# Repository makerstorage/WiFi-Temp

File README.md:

**WiFi Temperature Controller**

For more details, check out the product page at

http://makerstorage.com/index.php?id_product=27&controller=product

MakerStorage invests time and resources providing this open source design, please support MakerStorage and open-source hardware by purchasing products from MakerStorage!

Designed by MakerStorage LLC.

Creative Commons Attribution, Share-Alike license, check https://creativecommons.org/licenses/by-sa/3.0/ for more information All text above must be included in any redistribution

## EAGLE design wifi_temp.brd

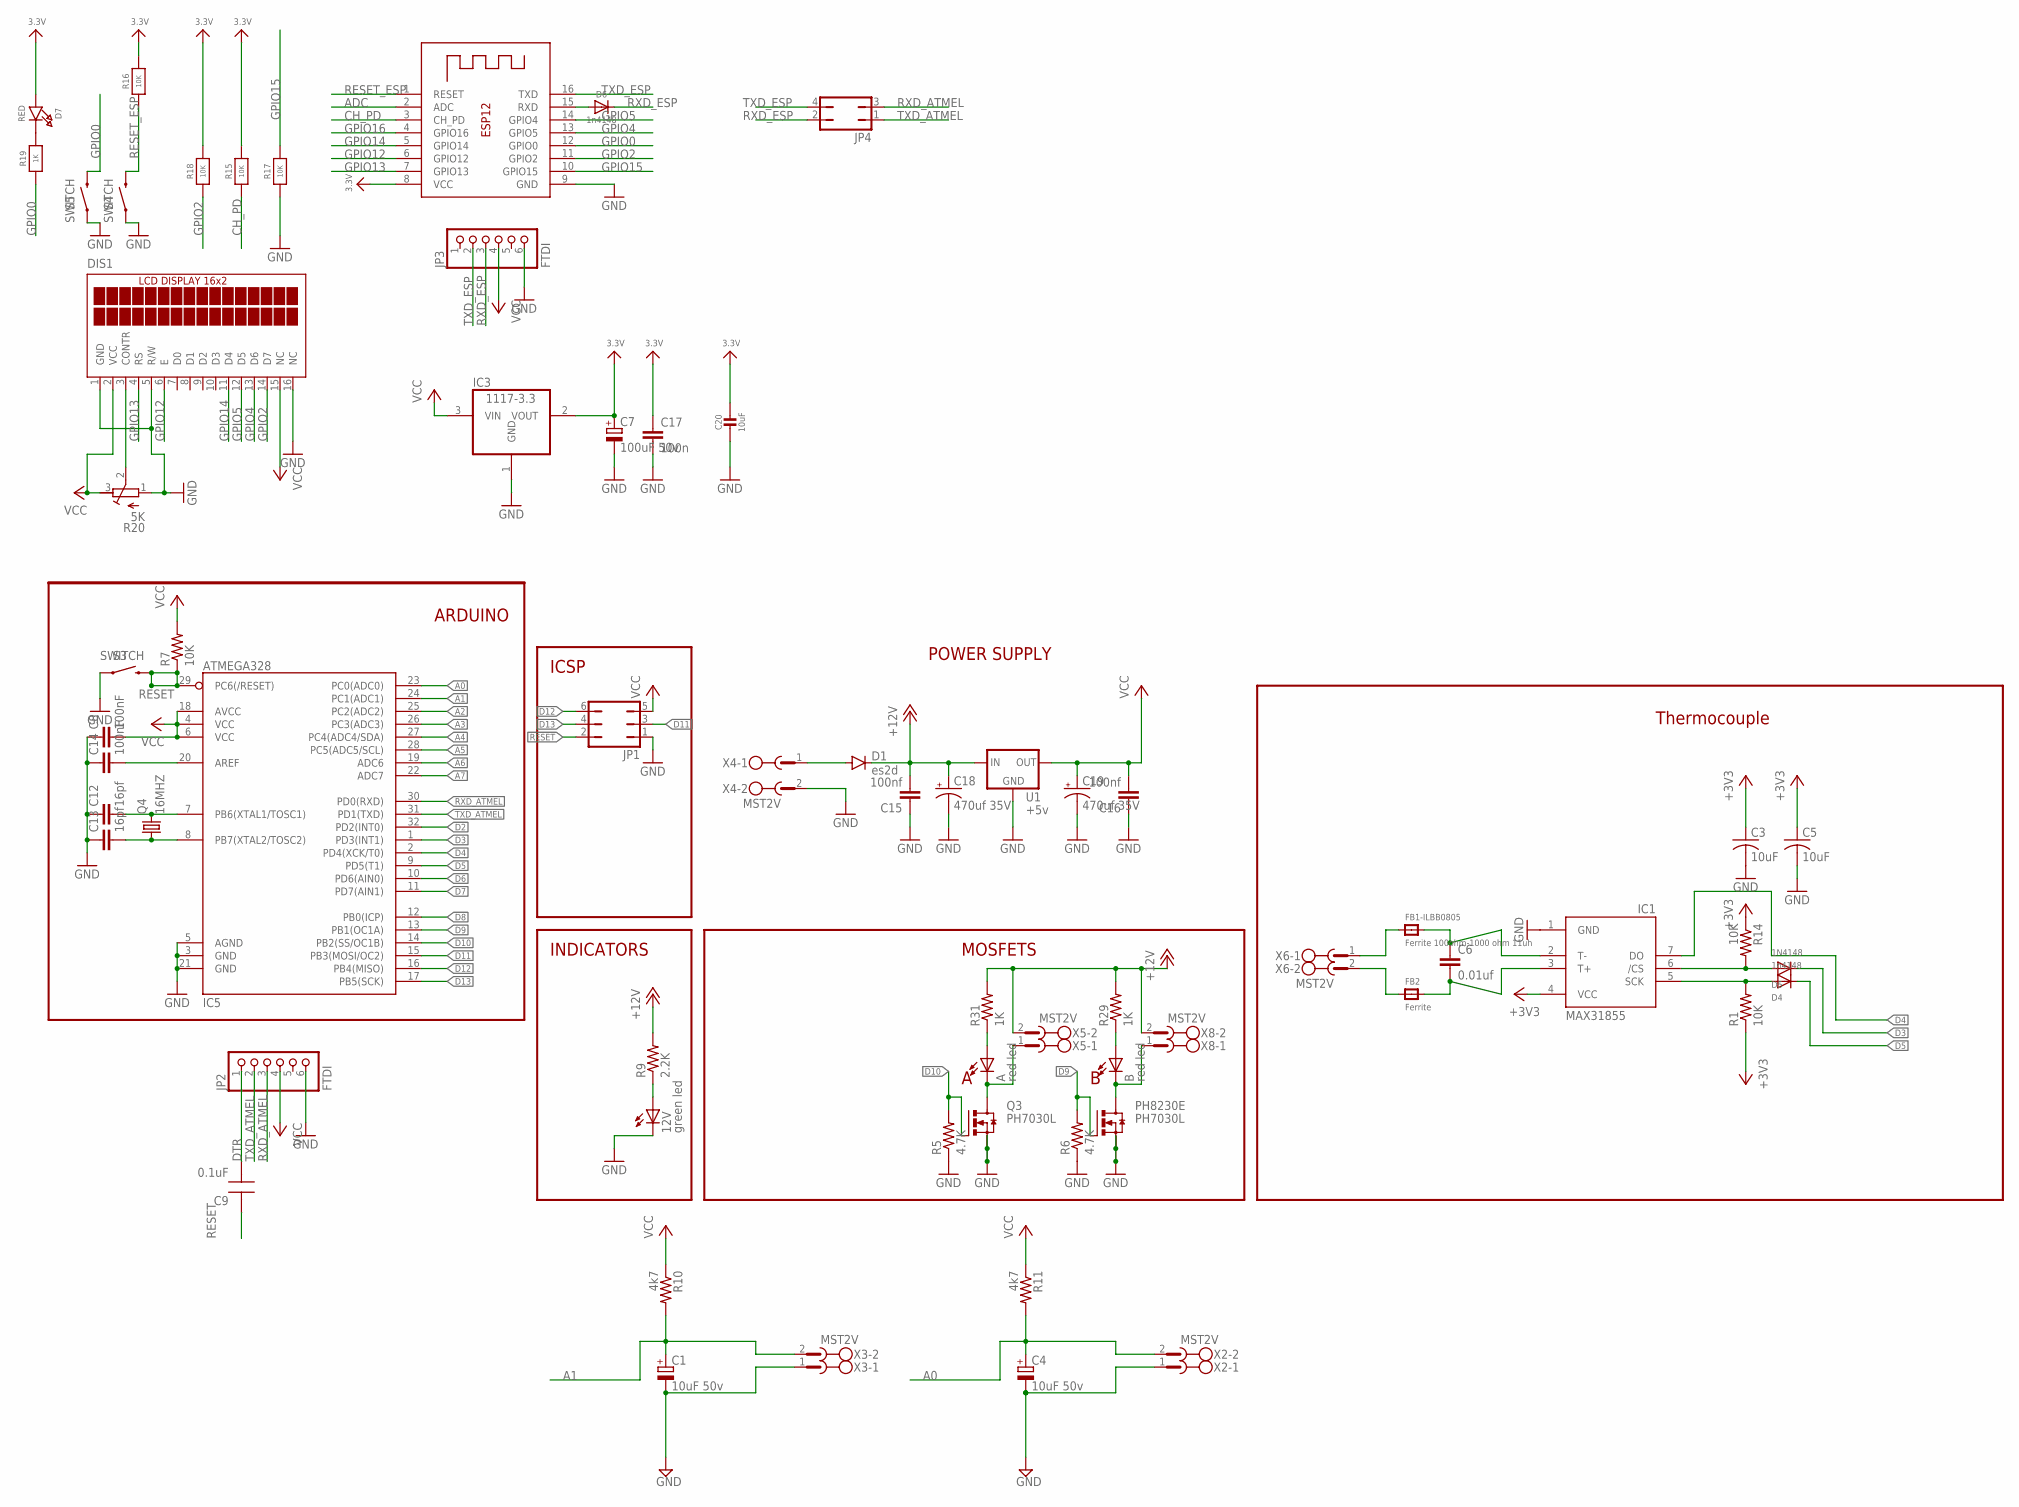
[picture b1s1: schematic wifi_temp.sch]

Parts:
12V: green led; LED-0805
A: red led; LED-0805
B: red led; LED-0805
C1, C4: 10uF 50v; SANYO-OSCON_SMD_B6
C3, C5: 10uF; C0805K
C6: 0.01uf; 0805
C7: 100uF 50v; SANYO-OSCON_SMD_E12
C8, C14: 100nF; 0805
C9: 0.1uF; CAP0805-NP
C12, C13: 16pf; 0805
C15, C16: 100nf; C0805
C17: 100n; C0805
C18, C19: 470uf 35V; PANASONIC_G
C20: 10uF; 0805-NO
D1: es2d; SMA-DIODE_ALT
D4: 1n4148; SOD-323F
D5: 1N4148; SOD-323F
D6: 1n4148; SOD-323
D7: RED; CHIPLED_0805_NOOUTLINE
DIS1: TUXGR_16X2_R2
FB1-ILBB0805: Ferrite 100ohm-1000 ohm 11uh; _0805
FB2: Ferrite; _0805
IC1: MAX31855; SO08
IC3: 1117-3.3; SOT223
IC5: ATMEGA328; TQFP32-08
JP1: JP3Q
JP2, JP3: FTDI; 1X06_ROUND_70
JP4: JP2Q
PH8230E: PH7030L; SOT669
Q3: PH7030L; SOT669
Q4: 16MHZ; SM49
R1, R14: 10K; R0805
R5, R6: 4.7K; 0805
R7: 10K; 0805
R9: 2.2K; 0805
R10, R11: 4k7; 0805
R15, R16, R17, R18: 10K; 0805-NO
R19: 1K; 0805-NO
R20: 5K; RTRIM3103
R29, R31: 1K; 0805
S3, S4, S5: SWITCH; TACTILE-SWITCH-SMD
U1: +5v; TO-252
X2, X3, X4, X5, X6, X8: MST2V; MSTBV2
X7: ESP-12F; ESP-12

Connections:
3.3V: C3.1, C5.1, C7.+, C17.1, C20.1, D7.A, IC1.4 (VCC), IC3.2 (VOUT), R1.1, R14.1, R15.2, R16.2, R18.2, X7.8 (VCC)
+12V: C15.2, C18.+, D1.C, R9.2, R29.2, R31.2, U1.1 (IN), X5.2, X8.2
A0: C4.+, IC5.23 (PC0(ADC0)), R11.2, X2.2
A1: C1.+, IC5.24 (PC1(ADC1)), R10.2, X3.2
A2: IC5.25 (PC2(ADC2))
A3: IC5.26 (PC3(ADC3))
A4: IC5.27 (PC4(ADC4/SDA))
A5: IC5.28 (PC5(ADC5/SCL))
A6: IC5.19 (ADC6)
A7: IC5.22 (ADC7)
ADC: X7.2 (ADC)
APWR: A.C, Q3.MB (D), X5.1
BPWR: B.C, PH8230E.MB (D), X8.1
CH_PD: R15.1, X7.3 (CH_PD)
CS: D5.A, IC1.6 (/CS), R14.2
D2: IC5.32 (PD2(INT0))
D3: D5.C, IC5.1 (PD3(INT1))
D4: IC1.7 (DO), IC5.2 (PD4(XCK/T0))
D5: D4.C, IC5.9 (PD5(T1))
D6: IC5.10 (PD6(AIN0))
D7: IC5.11 (PD7(AIN1))
D8: IC5.12 (PB0(ICP))
D9: IC5.13 (PB1(OC1A)), PH8230E.4 (G), R6.2
D10: IC5.14 (PB2(SS/OC1B)), Q3.4 (G), R5.2
D11: IC5.15 (PB3(MOSI/OC2)), JP1.3
D12: IC5.16 (PB4(MISO)), JP1.6
D13: IC5.17 (PB5(SCK)), JP1.4
DTR: C9.2, JP2.1
GND: 12V.C, C1.-, C3.2, C4.-, C5.2, C7.-, C8.1, C12.1, C13.1, C14.1, C15.1, C16.1, C17.2, C18.-, C19.-, C20.2, DIS1.1 (GND), DIS1.5 (R/W), DIS1.16 (NC), IC1.1 (GND), IC3.1 (GND), IC5.3 (GND), IC5.5 (AGND), IC5.21 (GND), JP1.1, JP2.6, JP3.6, PH8230E.1 (S), PH8230E.2 (S), PH8230E.3 (S), Q3.1 (S), Q3.2 (S), Q3.3 (S), R5.1, R6.1, R17.1, R20.1 (A), S3.1, S3.2 (1), S4.1, S4.2 (1), S5.1, S5.2 (1), U1.3 (GND), X2.1, X3.1, X4.2, X7.9 (GND)
GPIO0: R19.1, S5.3 (2), S5.4 (2), X7.12 (GPIO0)
GPIO2: DIS1.14 (D7), R18.1, X7.11 (GPIO2)
GPIO4: DIS1.13 (D6), X7.13 (GPIO5)
GPIO5: DIS1.12 (D5), X7.14 (GPIO4)
GPIO12: DIS1.6 (E), X7.6 (GPIO12)
GPIO13: DIS1.4 (RS), X7.7 (GPIO13)
GPIO14: DIS1.11 (D4), X7.5 (GPIO14)
GPIO15: R17.2, X7.10 (GPIO15)
GPIO16: X7.4 (GPIO16)
unnamed: FB1-ILBB0805.1, X6.1
unnamed: C6.2, FB2.2, IC1.3 (T+)
unnamed: D1.A, X4.1
unnamed: DIS1.3 (CONTR), R20.2 (S)
unnamed: C6.1, FB1-ILBB0805.2, IC1.2 (T-)
unnamed: FB2.1, X6.2
unnamed: D7.C, R19.2
unnamed: D6.A, X7.15 (RXD)
unnamed: C14.2, IC5.20 (AREF)
unnamed: 12V.A, R9.1
unnamed: C12.2, IC5.7 (PB6(XTAL1/TOSC1)), Q4.2
unnamed: C13.2, IC5.8 (PB7(XTAL2/TOSC2)), Q4.1
unnamed: A.A, R31.1
unnamed: B.A, R29.1
RESET: C9.1, IC5.29 (PC6(/RESET)), JP1.2, R7.1, S3.3 (2), S3.4 (2)
RESET_ESP: R16.1, S4.3 (2), S4.4 (2), X7.1 (RESET)
RXD_ATMEL: IC5.30 (PD0(RXD)), JP2.3, JP4.3
RXD_ESP: D6.C, JP3.3, JP4.2
SCK: D4.A, IC1.5 (SCK), R1.2
TXD_ATMEL: IC5.31 (PD1(TXD)), JP2.2, JP4.1
TXD_ESP: JP3.2, JP4.4, X7.16 (TXD)
VCC: C8.2, C16.2, C19.+, DIS1.2 (VCC), DIS1.15 (NC), IC3.3 (VIN), IC5.4 (VCC), IC5.6 (VCC), IC5.18 (AVCC), JP1.5, JP2.4, JP3.4, R7.2, R10.1, R11.1, R20.3 (E), U1.2 (OUT)

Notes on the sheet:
MOSFETS
ICSP
ARDUINO
INDICATORS
POWER SUPPLY
Thermocouple

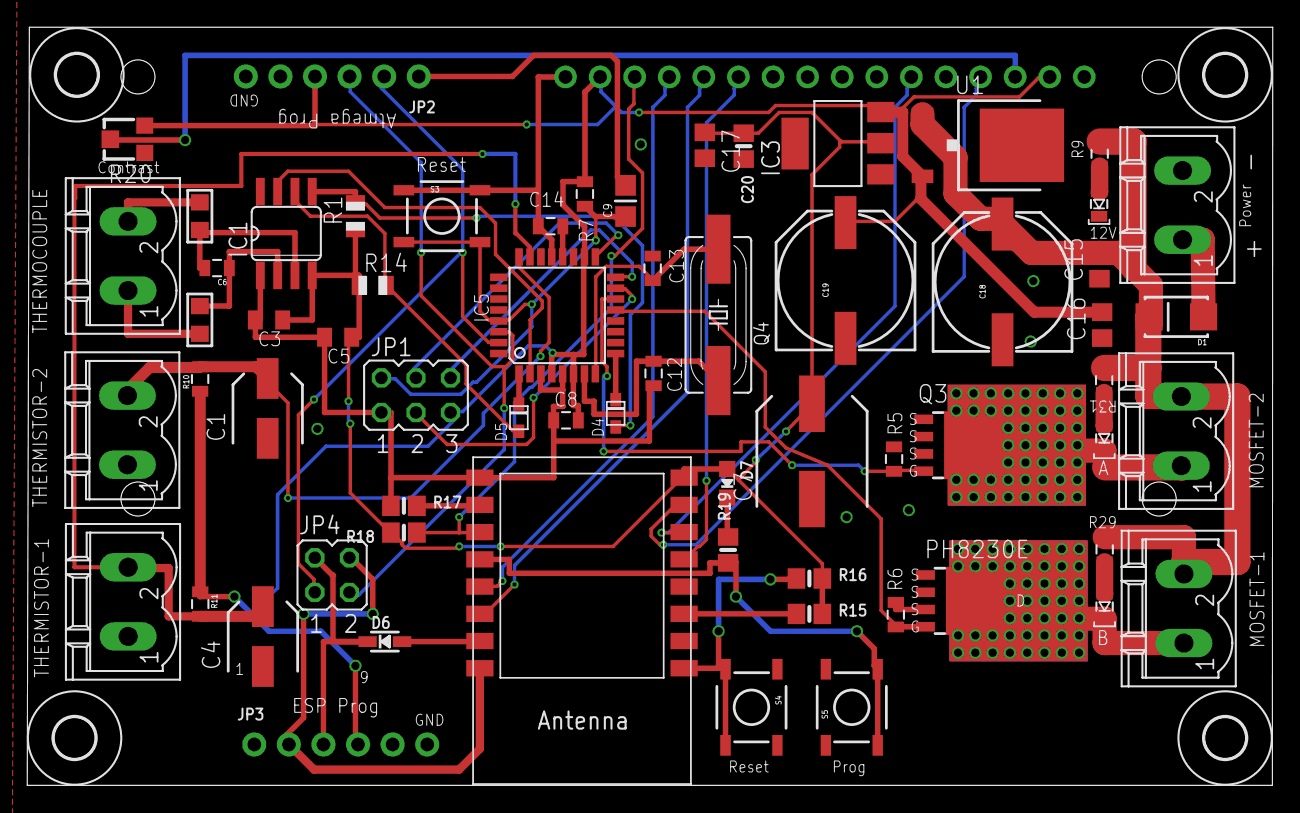
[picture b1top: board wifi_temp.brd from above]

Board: 2 copper layers, 91.5 x 55.7 mm, 69 parts (1 on the bottom side), 48 nets.

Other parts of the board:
U$1, U$2, U$3, U$4: 3,0

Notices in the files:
parts and their libraries:
microbuilder: This work is placed in the public domain, and may be freely used for commercial and non-commercial work with the following conditions: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
SparkFun-Electromechanical: Licensing: Creative Commons ShareAlike 4.0 International - https://creativecommons.org/licenses/by-sa/4.0
